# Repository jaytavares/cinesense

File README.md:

# Cinesense: an Audio Sensing Add-on for Bose Cinemate Speakers

## Overview

Do you have Bose Cinemate speakers? Do you wish they would just turn on automatically when you need them
and turn off when you're done. This project provides everything you need to do just that. Using it, you can create an
adapter that plugs into the interface module cable and adds audio sensing capability to your Bose Cinemate speakers.\*

\* This project only works with Bose Cinemate **Series II** speakers. Since the Cinemate Series I speakers don't have an optical audio input, the Cinesense will not work with them.

[Buy One!](#buy-one)

[Build It!](#the-parts-list)

## What People are Saying

> Amazing! Works perfectly. Didn’t expect it to auto shutoff after a couple of seconds when the source is powered off, so that’s a plus! Thanks again! _— Chris T._

> Just received it and installed it. What an awesome little gadget! Thanks for doing this for us and sending some joy our way. It may be a small thing. But pretty awesome! _— Jennifer S._

> Works like a charm! Thanks very much again. _— Miroslav V._

> Hey- just wanted to tell you the adapter works great! Thanks again! _— Graham L._

> Hey the adapter is installed and works great, thanks for making one for me, it's worth paying you for your ingenuity. I'm so much happier not having any remotes since I use google voice to do everything else other than volume changes. _— Enrique I._

> They work perfectly, thank you so much! _— David A._

> Received it today and it works as described. Thanks again! _— Jeremiah O._

> You’ve changed my life Jay!!!! Thank you!! _— Nathan R._

> The adapter works great! Thanks again Jay. _— Dmitrij P._

> Just got it in the mail, it's amazing!! Thank you so much! Timing was impeccable.. I literally was just looking at new speakers now I don't have to! You have no idea how happy this makes me haha _— Julie C._

> Dude, you’re a wizard! Love this thing. Who knew something so simple looking could be so helpful? Thanks again! _— Brian W._

### How It Works

When placed inline between the sub woofer module and the interface module, the Cinesense adapter repeatedly polls the
optical audio input for a signal. When a signal is sensed, the speakers are automatically turned on. The adapter will
continue to monitor the signal while the speakers are in use. Once the signal has stopped for ten seconds, the adapter
will turn the speakers off.

NOTE: The adapter only looks at the optical input and will not respond to audio signals on the analog inputs. This is a
potential future enhancement that can be made to the design. Also, the term "Audio Signal" here is referring to optical
audio "data" which is not the same as "sound". It's possible for the optical audio signal to be present _and_ silent
(e.g. music player is powered on but is paused).

Aside from the new found ability to automatically turn on and off in response to the audio signal, all aspects of the
speakers are the same. You can still use your remote to control the volume and mute the speakers. You can even use your
remote to turn the speakers off, though if there is an audio signal present, they'll just turn right back on again.

## Theory of Operation (for nerds)

Below I've included not just how the Cinesense works but everything I learned about these speakers in the course
of building this project. Hopefully it will be helpful to someone else interested in hacking these speakers.

Some notes:

- Pin 4 - Interface module CONTROL LINE
  - Has three possible states
    - LOW - power off
    - HIGH - power on, LED on
    - FLOAT - power on, LED off
      - This is how the LED is able to flash when the speakers are muted and in response to remote button presses.
      - This allows us to turn on the optical input without also turning on the LED in the interface module. 👍
- Pin 8 - Optical audio
  - Digital audio data (Didn't seem to be at the same 3.3v logic level--it was lower.)
- Pin 9 - IR Line
  - Decoded IR data (NEC protocol) with no carrier frequency

As you can see in the diagram above, the micro-controller interrupts the control line in order to allow independent control of the interface
module. The control line input can be polled to determine the power state of the speakers, the resistors on the control
line input act as a voltage divider allowing the micro-controller to accurately detect the floating state. By floating
the control line output, the interface module can be turned on without lighting its LED or turning on the speakers. This
supplies power to the optical input and allows us to check for a signal.

In my experimentation, it didn't appear that I could turn on the speakers by simply bringing the control line high. So,
instead, when an audio signal is sensed, I inject the 'ON' infrared command directly into the IR Line. This simulates
pressing the on button on the remote and the speaker system powers on in turn. Since we are tapping into the IR data line
directly, we need only inject the command itself with no carrier frequency. These speakers use the NEC IR protocol.
Here are the commands that they support:

- 0x5D0532CD On/Off
- 0x5D05C03F Vol. Up
- 0x5D0540BF Vol. Down
- 0x5D05807F Mute

## Buy One

[Click here for the latest information on availability.](./BUY_ONE.md)

## The Parts List

You'll need a few parts:

### The PCB

- 1x [Printed circuit board](https://oshpark.com/shared_projects/PZXtdoM9)

### The Components

Fast order: Click for a shopping cart with all the needed components

[Digi-Key](https://www.digikey.com/short/znq4vb) | [Mouser](https://www.mouser.com/ProjectManager/ProjectDetail.aspx?AccessID=052330197b)

- 1x Dual sided hood
- 1x DB9 Male connector
- 1x DB9 Female connector
- 1x ATTINY85 microchip
- 2x 1㏁ resistors
- 1x 1µF capacitor
- 1x 2x3 header (_Optional_--only needed if you plan to program the chip on the board.)

## The Tools

You'll need soldering supplies to assemble the board and a way to program the microchip. I use the [Pocket AVR Programmer](https://www.sparkfun.com/products/9825) from SparkFun.

## The Circuit Board

### Quick & Easy

For convenience, You can purchase the board on [OSHPark](https://oshpark.com/shared_projects/PZXtdoM9).

### Schematic and Board layout file

The board was originally designed in EAGLE CAD, but Autodesk has discontinued EAGLE and the files are now best viewed in Fusion. If you need to inspect or modify the design, you will find the original CAD files in the [board](./board) folder.

For convenience, viewable schematic files have been included in the [schematic](./schematic) folder for anyone who does not have access to Fusion.

### Assembly

Before you start assembly, be sure to file off any tabs left on your boards as a result of panelization. If you skip this
step, you'll have trouble fitting the completed board into the housing. This is especially important for tabs along the
short edges where the DB9 connectors attach. After removing the tabs, I dry fit the connectors on the board and placed
everything in one half of the housing. I was then able to tack solder the connectors in place to ensure the final
assembly would fit in the housing.

## The Software

### Use Precompiled software (Easiest option)

1.  Download the most recent `firmware.hex` file from the [Releases](https://github.com/jaytavares/cinesense/releases) page.
2.  Connect your AVR Programmer to the chip. (I've included an ISP header on the board if you don't have a standalone programmer for ATTINY chips.)
3.  Use [avrdude](http://savannah.nongnu.org/projects/avrdude/) to program the ATTINY chip. Assuming you're using the "Pocket AVR Programer", run:

```
$ avrdude -c usbtiny -p t85 -U lfuse:w:0xe2:m -U hfuse:w:0xdf:m -U efuse:w:0xff:m -U flash:w:firmware.hex:i
```

### Build from the source (Most flexible option)

If you would like to customize your Cinesense, you'll have to build the software from the source. The software for this project is built using the fantastic [PlatformIO](https://platformio.org).

#### Programming the chip

1.  Connect your AVR Programmer to the chip. (I've included an ISP header on the board if you don't have a standalone programmer for ATTINY chips.)
2.  In the root directory of this project, run:

```
platformio run
```

This should compile the software, burn the correct fuses, and upload the software to the chip.

## Legal

This project is licensed under the MIT License. See [LICENSE.txt](LICENSE.txt) for more information. "Bose" and "Cinemate" are registered trademarks of Bose Corporation, Framingham, MA. This project is not endorsed by or affiliated with the Bose Corporation.

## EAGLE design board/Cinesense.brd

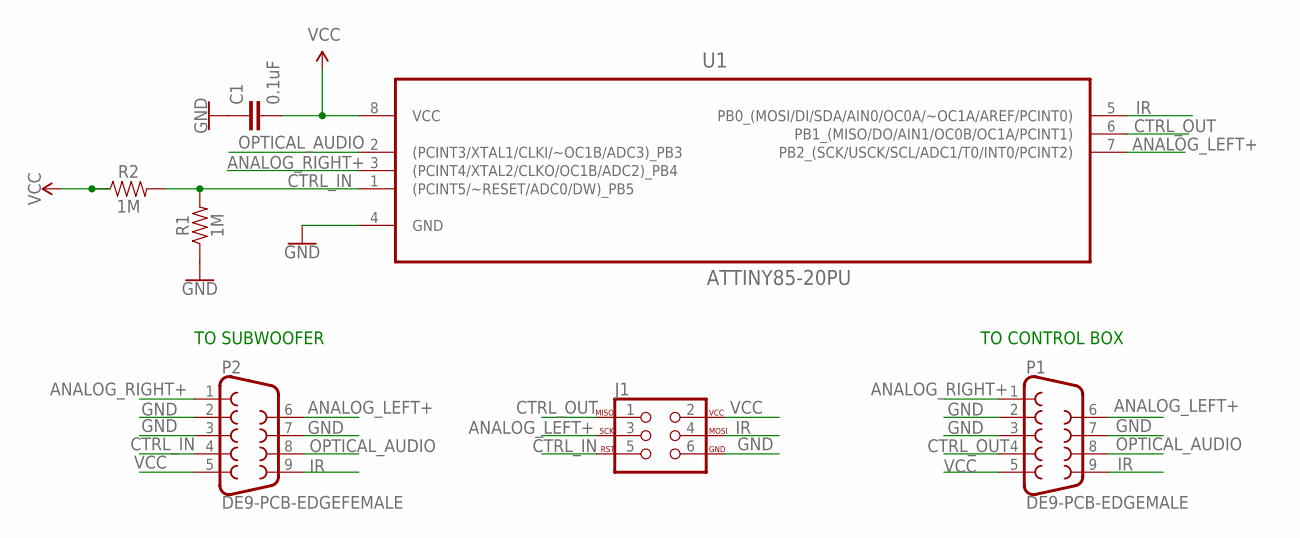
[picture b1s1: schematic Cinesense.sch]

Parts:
C1: 0.1uF; CAP-PTH-SMALL-KIT
J1: AVR_SPI_PROG_3X2PTH; 2X3
P1: DE9-PCB-EDGEMALE; DE9-EDGE-M
P2: DE9-PCB-EDGEFEMALE; DE9-EDGE-F
R1, R2: 1M; AXIAL-0.3
U1: ATTINY85-20PU; DIP254P762X533-8

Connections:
ANALOG_LEFT+: J1.3, P1.6, P2.6, U1.7 (PB2_(SCK/USCK/SCL/ADC1/T0/INT0/PCINT2))
ANALOG_RIGHT+: P1.1, P2.1, U1.3 ((PCINT4/XTAL2/CLKO/OC1B/ADC2)_PB4)
CTRL_IN: J1.5, P2.4, R1.P$2 (2), R2.P$2 (2), U1.1 ((PCINT5/~RESET/ADC0/DW)_PB5)
CTRL_OUT: J1.1, P1.4, U1.6 (PB1_(MISO/DO/AIN1/OC0B/OC1A/PCINT1))
GND: C1.1, J1.6, P1.2, P1.3, P1.7, P2.2, P2.3, P2.7, R1.P$1 (1), U1.4 (GND)
IR: J1.4, P1.9, P2.9, U1.5 (PB0_(MOSI/DI/SDA/AIN0/OC0A/~OC1A/AREF/P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)
OPTICAL_AUDIO: P1.8, P2.8, U1.2 ((PCINT3/XTAL1/CLKI/~OC1B/ADC3)_PB3)
VCC: C1.2, J1.2, P1.5, P2.5, R2.P$1 (1), U1.8 (VCC)

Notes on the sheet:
TO SUBWOOFER
TO CONTROL BOX

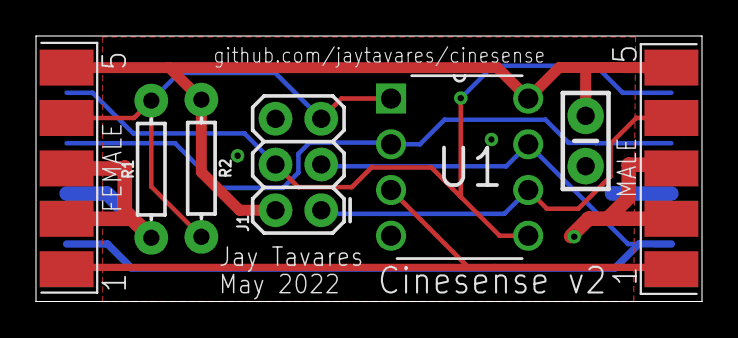
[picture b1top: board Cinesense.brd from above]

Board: 2 copper layers, 37.0 x 14.8 mm, 7 parts (0 on the bottom side), 8 nets.

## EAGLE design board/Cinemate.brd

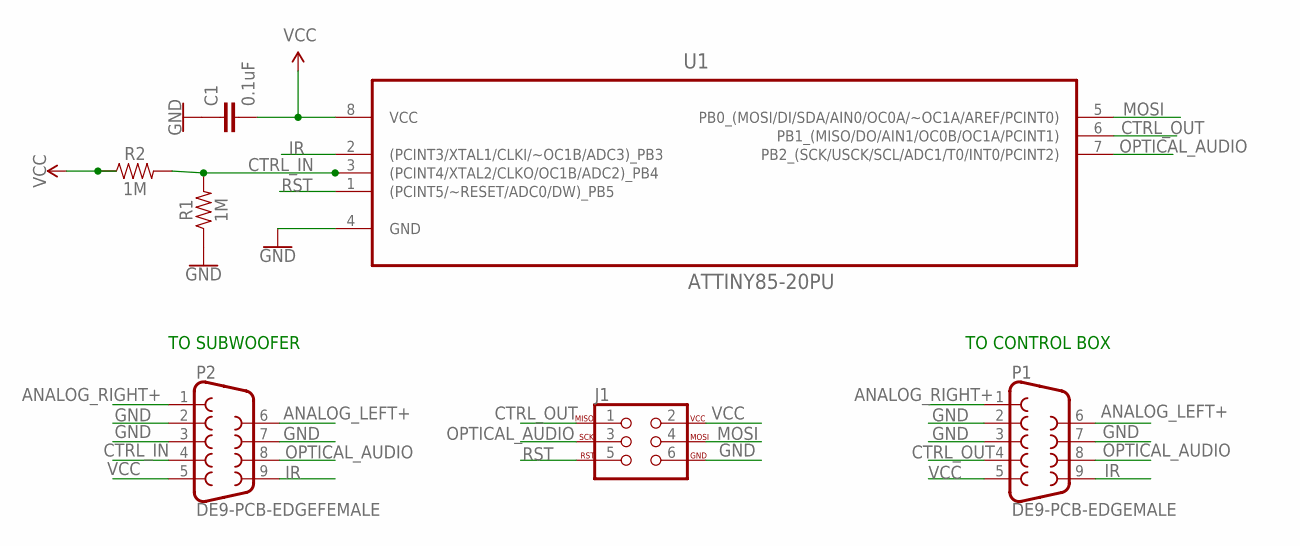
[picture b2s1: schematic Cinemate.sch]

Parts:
C1: 0.1uF; CAP-PTH-SMALL-KIT
J1: AVR_SPI_PROG_3X2PTH; 2X3
P1: DE9-PCB-EDGEMALE; DE9-EDGE-M
P2: DE9-PCB-EDGEFEMALE; DE9-EDGE-F
R1, R2: 1M; AXIAL-0.3
U1: ATTINY85-20PU; DIP254P762X533-8

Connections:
ANALOG_LEFT+: P1.6, P2.6
ANALOG_RIGHT+: P1.1, P2.1
CTRL_IN: P2.4, R1.P$2 (2), R2.P$2 (2), U1.3 ((PCINT4/XTAL2/CLKO/OC1B/ADC2)_PB4)
CTRL_OUT: J1.1, P1.4, U1.6 (PB1_(MISO/DO/AIN1/OC0B/OC1A/PCINT1))
GND: C1.1, J1.6, P1.2, P1.3, P1.7, P2.2, P2.3, P2.7, R1.P$1 (1), U1.4 (GND)
IR: P1.9, P2.9, U1.2 ((PCINT3/XTAL1/CLKI/~OC1B/ADC3)_PB3)
MOSI: J1.4, U1.5 (PB0_(MOSI/DI/SDA/AIN0/OC0A/~OC1A/AREF/P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)
OPTICAL_AUDIO: J1.3, P1.8, P2.8, U1.7 (PB2_(SCK/USCK/SCL/ADC1/T0/INT0/PCINT2))
RST: J1.5, U1.1 ((PCINT5/~RESET/ADC0/DW)_PB5)
VCC: C1.2, J1.2, P1.5, P2.5, R2.P$1 (1), U1.8 (VCC)

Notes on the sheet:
TO SUBWOOFER
TO CONTROL BOX

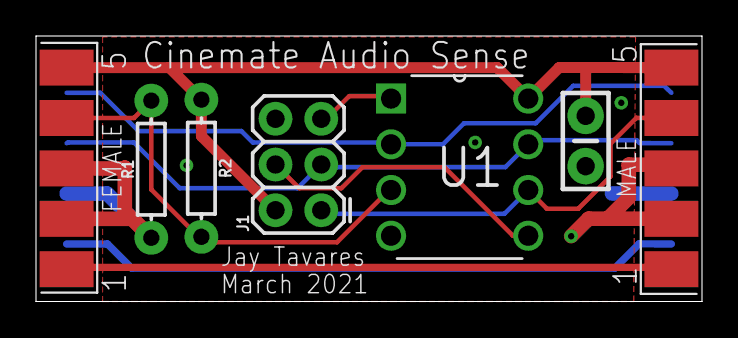
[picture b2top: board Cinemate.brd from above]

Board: 2 copper layers, 37.0 x 14.8 mm, 7 parts (0 on the bottom side), 10 nets.

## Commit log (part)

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2019-09-14 Ignore cmake-build-debug folder
2019-09-14 Clean up NEC send code
2020-01-10 Rename sketch files
2020-01-11 Fix audio signal sensing
2020-01-11 Add note about hi-Z control_in pin, speed up loop
2020-01-11 Add ir code
2020-01-11 First working version with automatic power on
2020-01-11 Add automatic power off
2020-01-11 Enable toggling of serial debugging
2020-01-11 Fix typo
2020-01-11 Disable automatic power off
2020-01-14 Tweak timing, remove auto off
2020-01-15 Convert project to platformio
2020-01-16 Add accurate control in line monitoring
2020-01-16 Add audio sensing and auto power back in
2020-01-16 Move stuff into header files
2020-01-16 Add auto-off feature
2020-01-16 Alter .gitignore
2020-02-06 Add Eagle files & readme
2020-02-06 Set default targets for pio run, add more instructions to readme
2020-02-07 Update header link to digikey part
2020-02-08 Update README
    Add license information, Add programming instructions.
2020-02-08 Add license file
2020-02-08 Add "How it works" section to the README
2020-02-08 Update name of hex file
2020-02-09 Add theory of operation
2020-02-11 Add note about panelization tabs
2020-02-12 Remove unneded build directory
2020-02-13 Remove unneeded eagle files
2020-02-13 Remove unused directories
2020-03-23 Update resistor link in readme
2020-04-29 Change link to capacitor
2020-05-14 Add link to PCB in parts list
2020-05-19 Update project name
2020-05-27 Broaden ignored build folders
2020-06-02 Remove note about resistor--they fit
2020-06-03 Consolidate parts list to one supplier
2020-06-06 Update product links
    Fix incorrect female connector, change all links to Mouser for since some
    are out of stock at DigiKey.
2020-08-23 Add testimonials section
2020-10-13 Add BOM links for Digi-Key and Mouser
2020-12-12 Add testimonial
2020-12-23 Set theme jekyll-theme-tactile
2021-01-17 Update README.md
    Add purchase information
2021-01-20 Update README.md
    Change paypal link
2021-03-25 Update board & ignore .vscode
    Reduce length of board by 1 mm to allow for a better fit in the enclosure
2021-03-25 Rename Eagle files
2021-03-25 Add github link to board silkscreen
2021-03-25 Update OSHPark link in README
2021-04-06 Update README.md
    Cinemate Series I work around/notes.
2021-04-16 Updated Readme.md that includes Cinemate Series I workaround
    These changes allow the Cinemate Series I to work with the circuit with minor changes.
2021-08-12 Clarify incompatibility with Series I speakers
2021-09-30 Update PayPal link
2021-11-01 Added code changes from @OKLakeGoer
2021-11-01 Fix link to Series I notes
2022-01-23 Update README with waiting list link
2022-04-12 Hold CONTROL_IN line low on initial start up
    Prevents speaker lock out, fixes #1
2022-04-13 A little code cleanup
2022-04-13 Add tagged-release Github action
2022-04-15 Update README.md
    Add note about limited-time adapter availability
2022-04-15 Add BUY_ONE readme
    Separate for ease of linking
2022-04-15 Update BUY_ONE.md
    Add information on backorder
2022-04-21 Add board file to releases
2022-05-24 Connect analog audio signals to inputs
2022-07-06 Peg platformio version in CI script
    Fixes: #6
2022-07-08 Specify more versions
    Platform and CI auto-release action
2022-10-07 Close sales, reopen waitlist
2022-10-17 Add note about pricing
2022-12-06 Reopen sales
2022-12-20 Add info to GH page
2023-07-07 Revert "Update readme"
    This reverts commit 832caea3b97bc6bcaf6c1b41ae3417c85ae16448.
2023-07-07 Update purchase information
2023-07-10 Update BUY_ONE.md
    Change purchase link to shortened url

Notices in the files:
parts and their libraries:
SparkFun-Connectors: Licensing: Creative Commons ShareAlike 4.0 International - https://creativecommons.org/licenses/by-sa/4.0
